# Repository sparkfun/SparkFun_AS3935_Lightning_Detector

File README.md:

SparkFun AS3935 Lightning Detector
========================================

[*SparkFun AS3935 Lightning Detector (SEN-15441)*](https://www.sparkfun.com/products/15441)

The SparkFun Lightning Detector adds lightning detection to your next weather station to make sure you are aware of any potential hazardous weather heading your way. The AS3935 is capable of detecting lightning up to 40km away with an accuracy of 1km to the storm front with a sensitive antenna tuned to pick up lightning events in the 500kHz band. 

There are a number of sources that can cause false positives but the lightning detector itself can reliably filter these out by default. If not, we've made sure to include settings you can configure using the lightning detector library to increase the chip's robustness to noise and false positives. The lightning detector library also gives you access to settings such as storm sensing sensitivity when detecting indoors vs outdoors, or the number of lightning strikes needed to trigger an interrupt.

Repository Contents
-------------------

* **/Documentation** - Datasheets, additional product information
* **/Hardware** - Eagle design files (.brd, .sch)

Documentation
--------------
* **[Installing an Arduino Library](https://learn.sparkfun.com/tutorials/installing-an-arduino-library/)** - Basic instructions on installing an Arduino library
* **[Library](https://github.com/sparkfun/SparkFun_AS3935_Lightning_Detector_Arduino_Library)** - Arduino library for the AS3935 Lightning Detector
* **[Hookup Guide](https://learn.sparkfun.com/tutorials/sparkfun-as3935-lightning-detector-hookup-guide-v20)** - Hookup Guide for the SparkFun AS3935 Lightning Detector

Product Versions
--------------
* [SEN-15441](https://www.sparkfun.com/products/15441) - SparkFun SPI version
* [SEN-15276](https://www.sparkfun.com/products/15276) - SparkFun I2C version
* [SPX-15057](https://www.sparkfun.com/products/retired/15057) - SparkX version

License Information
-------------------

This product is _**open source**_! 

Please review the LICENSE.md file for license information.

If you have any questions or concerns on licensing, please contact technical support on our [SparkFun forums](https://forum.sparkfun.com/viewforum.php?f=152).

Please use, reuse, and modify these files as you see fit. Please maintain attribution to SparkFun Electronics and release under the same license.

Distributed as-is; no warranty is given.

- Your friends at SparkFun.

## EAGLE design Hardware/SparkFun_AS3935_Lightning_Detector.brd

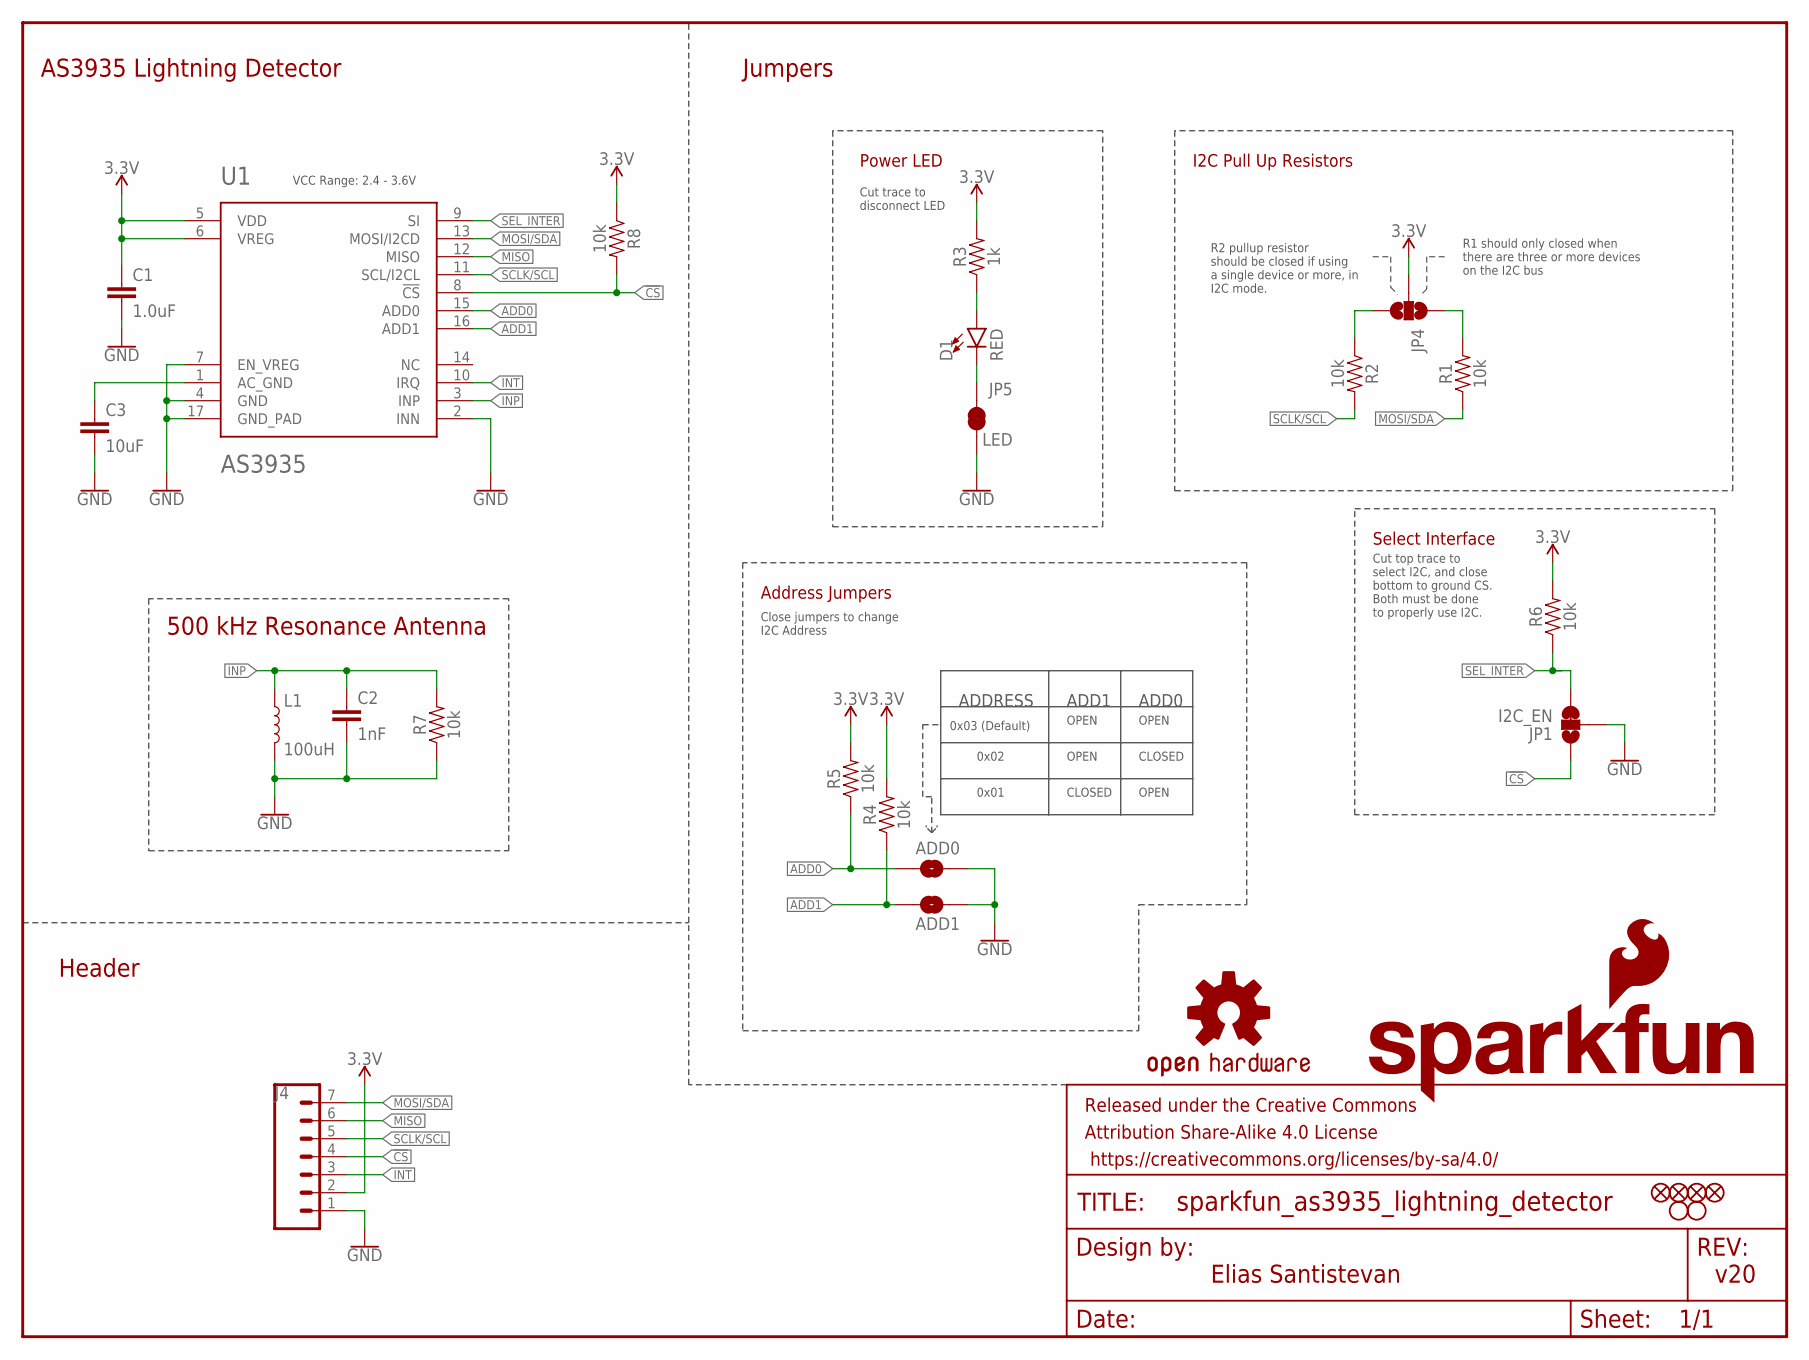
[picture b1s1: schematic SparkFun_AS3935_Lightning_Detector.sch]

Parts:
ADD0, ADD1: JUMPER-SMT_2_NO_SILK; SMT-JUMPER_2_NO_SILK
C1: 1.0uF; 0603
C2: 1nF; 0603
C3: 10uF; 0603
D1: RED; LED-0603
FD1, FD2, FD3, FD4: FIDUCIAL1X2; FIDUCIAL-1X2
FRAME1: FRAME-LETTER; CREATIVE_COMMONS
H1, H2: STAND-OFFTIGHT; STAND-OFF-TIGHT
J4: CONN_07NO_SILK; 1X07_NO_SILK
JP1: I2C_EN; SMT-JUMPER_3_1-NC_TRACE_SILK
JP4: JUMPER-SMT_3_NO_SILK; SMT-JUMPER_3_NO_SILK
JP5: LED; SMT-JUMPER_2_NC_TRACE_SILK
L1: 100uH; MA5532-AE
LOGO1: OSHW-LOGOS; OSHW-LOGO-S
LOGO2: SFE_LOGO_NAME.1_INCH; SFE_LOGO_NAME_.1
LOGO3: SFE_LOGO_FLAME.2_INCH; SFE_LOGO_FLAME_.2
R1, R2, R4, R5, R6, R7, R8: 10k; 0603
R3: 1k; 0603
U1: AS3935; 16LD_MLPQ

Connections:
3.3V: C1.1, J4.2, JP4.2, R3.2, R4.2, R5.2, R6.2, R8.1, U1.5 (VDD), U1.6 (VREG)
!CS: J4.4, JP1.1, R8.2, U1.8 (!CS)
ADD0: ADD0.1, R5.1, U1.15 (ADD0)
ADD1: ADD1.1, R4.1, U1.16 (ADD1)
GND: ADD0.2, ADD1.2, C1.2, C2.2, C3.2, J4.1, JP1.2, JP5.1, L1.2, R7.1, U1.2 (INN), U1.4 (GND), U1.7 (EN_VREG), U1.17 (GND_PAD)
INP: C2.1, L1.1, R7.2, U1.3 (INP)
INT: J4.3, U1.10 (IRQ)
MISO: J4.6, U1.12 (MISO)
MOSI/SDA: J4.7, R1.1, U1.13 (MOSI/I2CD)
unnamed: D1.A, R3.1
unnamed: C3.1, U1.1 (AC_GND)
unnamed: JP4.1, R1.2
unnamed: JP4.3, R2.1
unnamed: D1.C, JP5.2
SCLK/SCL: J4.5, R2.2, U1.11 (SCL/I2CL)
SEL_INTER: JP1.3, R6.1, U1.9 (SI)

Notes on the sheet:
Elias Santistevan
v20
AS3935 Lightning Detector
Jumpers
Header
500 kHz Resonance Antenna
R1 should only closed when there are three or more devices on the I2C bus
Close jumpers to change I2C Address
ADD0
ADD1
OPEN
CLOSED
ADDRESS
0x03 (Default)
0x02
VCC Range: 2.4 - 3.6V
Cut trace to disconnect LED
0x01
R2 pullup resistor should be closed if using a single device or more, in I2C mode.
Power LED
I2C Pull Up Resistors
Address Jumpers
Select Interface
Cut top trace to select I2C, and close bottom to ground CS. Both must be done to properly use I2C.

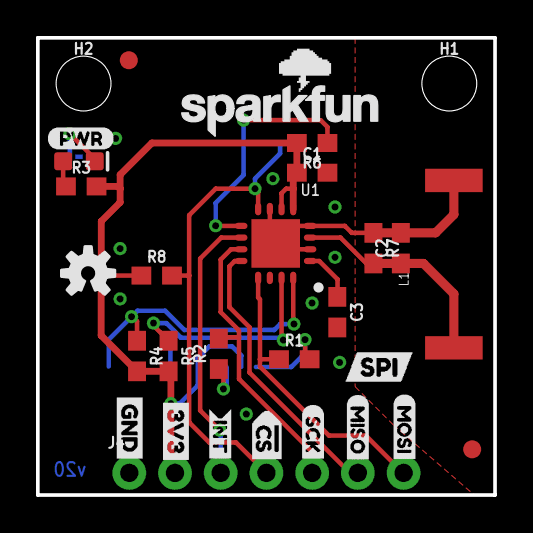
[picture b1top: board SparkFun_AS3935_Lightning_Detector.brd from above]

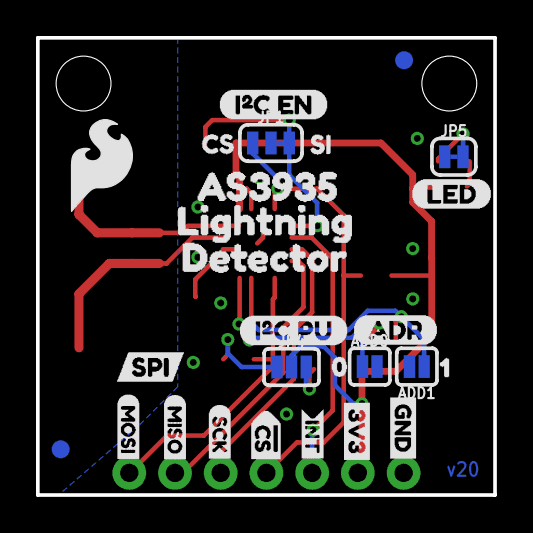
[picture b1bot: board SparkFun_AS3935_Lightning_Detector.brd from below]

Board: 2 copper layers, 25.4 x 25.4 mm, 59 parts (27 on the bottom side), 16 nets.

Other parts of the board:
U$1: LED0
U$2, U$10: GND-03
U$3, U$15: SPI1
U$4, U$18: 3V3-03
U$5, U$30: #CS0
U$6: AS39350
U$7: LIGHTNING0
U$8, U$23: SCK-(]-03
U$9, U$12: MISO-(]-03
U$11, U$22: MOSI-(]-03
U$13, U$14: INT0
U$16: CS0
U$17: I#C_EN0
U$19: SI1
U$32: PWR-()-03
U$33: ADR-()-04
U$34: I#C_PU0
U$36: 10
U$37: 00
U$39: DETECTOR0
U$40: ##0

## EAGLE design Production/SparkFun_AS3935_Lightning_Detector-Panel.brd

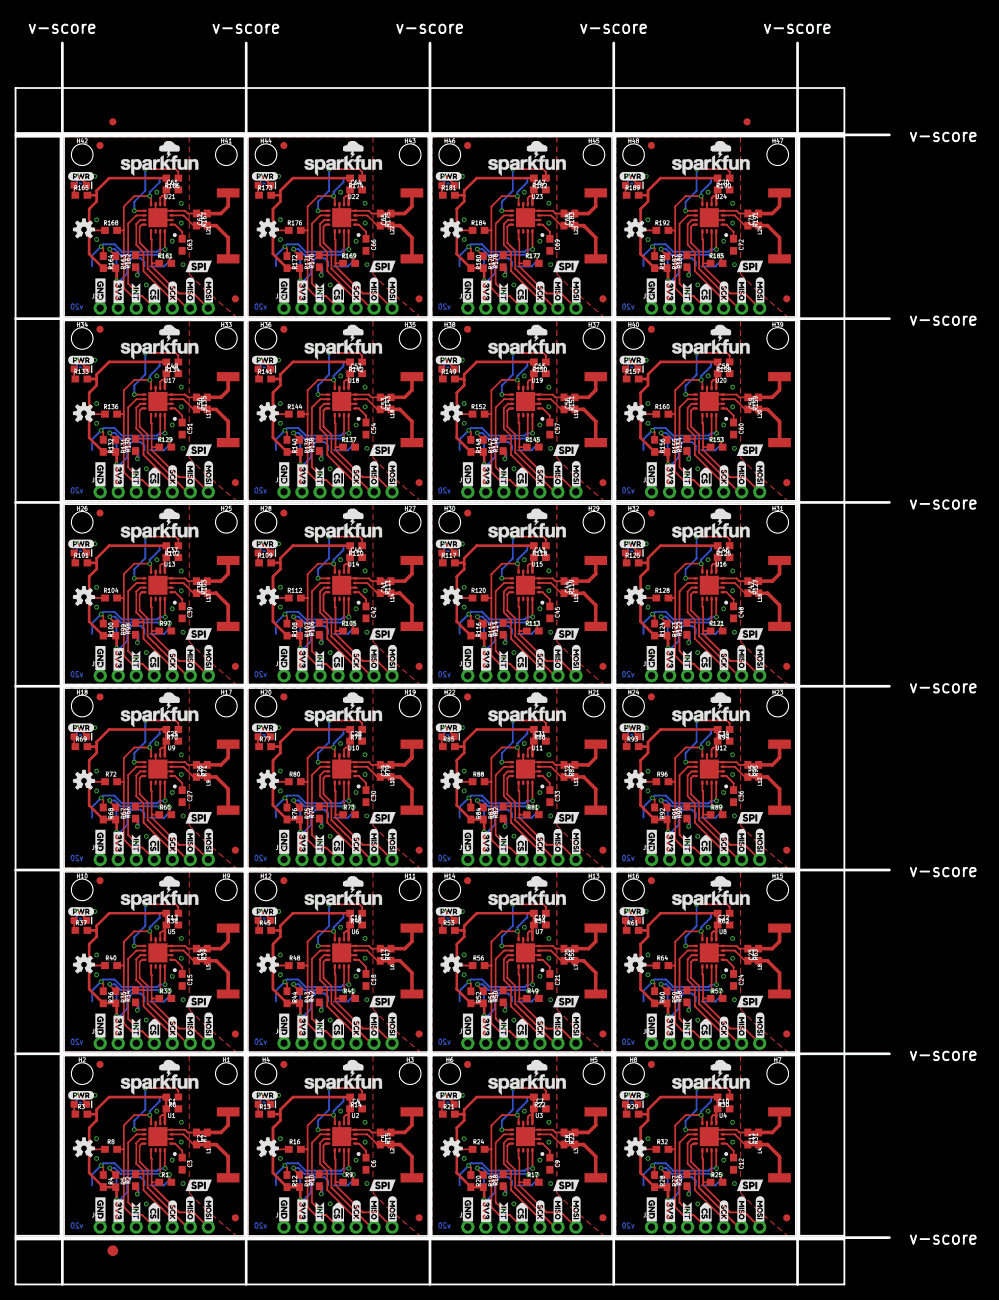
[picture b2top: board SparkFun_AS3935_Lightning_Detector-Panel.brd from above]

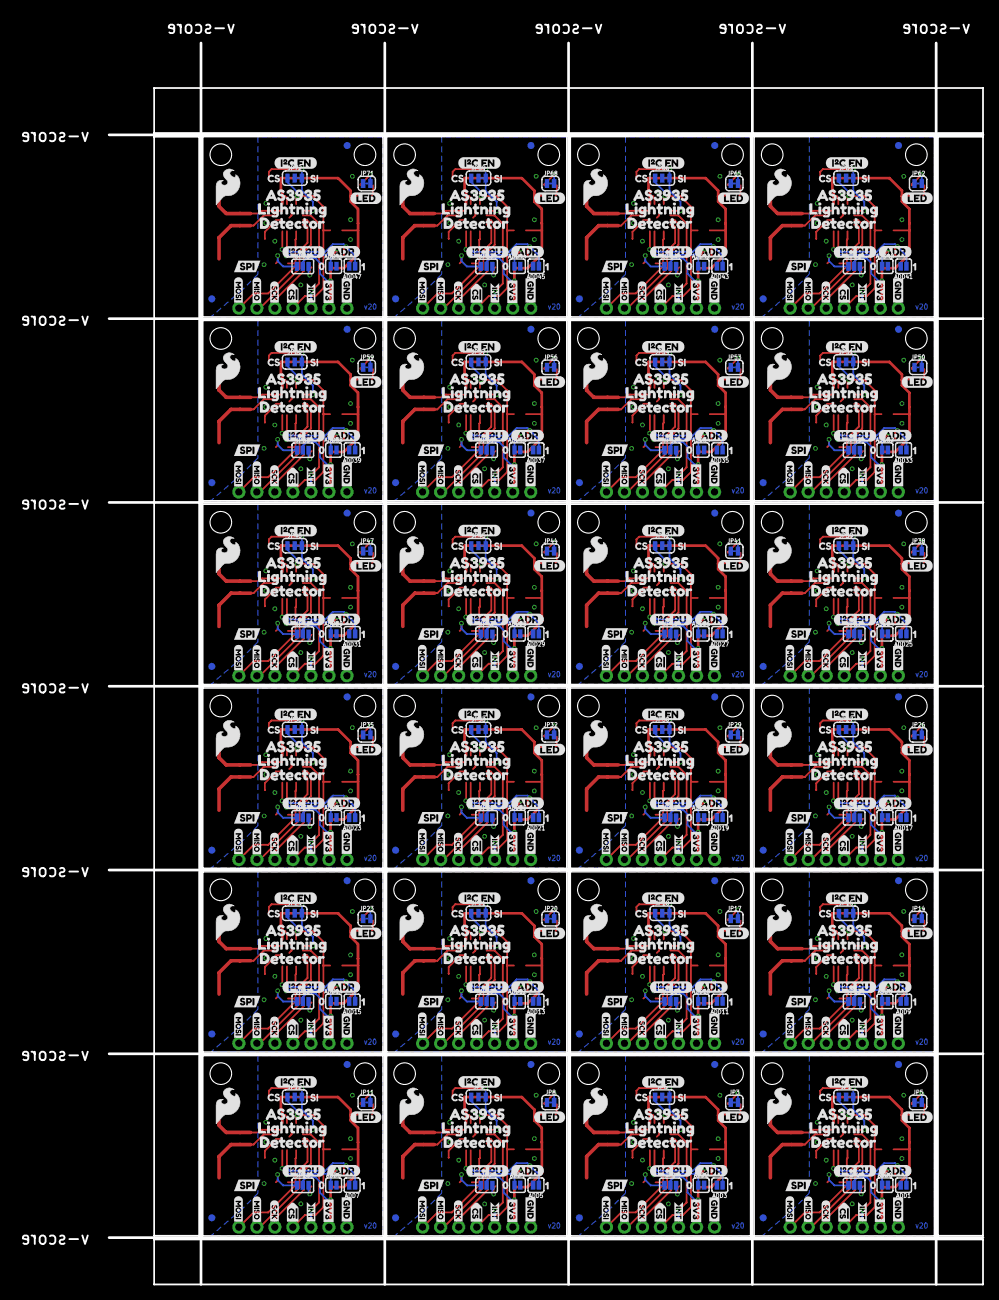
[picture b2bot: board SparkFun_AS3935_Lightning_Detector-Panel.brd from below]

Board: 2 copper layers, 136.4 x 178.9 mm, 1395 parts (648 on the bottom side), 384 nets.

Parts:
ADD0, ADD1, ADD2, ADD3, ADD4, ADD5, ADD6, ADD7, ADD8, ADD9, ADD10, ADD11, ADD12, ADD13, ADD14, ADD15, ADD16, ADD17, ADD18, ADD19, ADD20, ADD21, ADD22, ADD23, ADD24, ADD25, ADD26, ADD27, ADD28, ADD29, ADD30, ADD31, ADD32, ADD33, ADD34, ADD35, ADD36, ADD37, ADD38, ADD39, ADD40, ADD41, ADD42, ADD43, ADD44, ADD45, ADD46, ADD47: JUMPER-SMT_2_NO_SILK; SMT-JUMPER_2_NO_SILK
C1, C4, C7, C10, C13, C16, C19, C22, C25, C28, C31, C34, C37, C40, C43, C46, C49, C52, C55, C58, C61, C64, C67, C70: 1.0uF; 0603
C2, C5, C8, C11, C14, C17, C20, C23, C26, C29, C32, C35, C38, C41, C44, C47, C50, C53, C56, C59, C62, C65, C68, C71: 1nF; 0603
C3, C6, C9, C12, C15, C18, C21, C24, C27, C30, C33, C36, C39, C42, C45, C48, C51, C54, C57, C60, C63, C66, C69, C72: 10uF; 0603
D1, D2, D3, D4, D5, D6, D7, D8, D9, D10, D11, D12, D13, D14, D15, D16, D17, D18, D19, D20, D21, D22, D23, D24: RED; LED-0603
E$1, E$2: FIDUCIAL-1X2
E$3: FIDUCIAL-1.5X3
FD1, FD2, FD3, FD4, FD5, FD6, FD7, FD8, FD9, FD10, FD11, FD12, FD13, FD14, FD15, FD16, FD17, FD18, FD19, FD20, FD21, FD22, FD23, FD24, FD25, FD26, FD27, FD28, FD29, FD30, FD31, FD32, FD33, FD34, FD35, FD36, FD37, FD38, FD39, FD40, FD41, FD42, FD43, FD44, FD45, FD46, FD47, FD48, FD49, FD50, FD51, FD52, FD53, FD54, FD55, FD56, FD57, FD58, FD59, FD60, FD61, FD62, FD63, FD64, FD65, FD66, FD67, FD68, FD69, FD70, FD71, FD72, FD73, FD74, FD75, FD76, FD77, FD78, FD79, FD80, FD81, FD82, FD83, FD84, FD85, FD86, FD87, FD88, FD89, FD90, FD91, FD92, FD93, FD94, FD95, FD96: FIDUCIAL1X2; FIDUCIAL-1X2
H1, H2, H3, H4, H5, H6, H7, H8, H9, H10, H11, H12, H13, H14, H15, H16, H17, H18, H19, H20, H21, H22, H23, H24, H25, H26, H27, H28, H29, H30, H31, H32, H33, H34, H35, H36, H37, H38, H39, H40, H41, H42, H43, H44, H45, H46, H47, H48: STAND-OFFTIGHT; STAND-OFF-TIGHT
J1, J2, J3, J4, J5, J6, J7, J8, J9, J10, J11, J12, J13, J14, J15, J16, J17, J18, J19, J20, J21, J22, J23, J24: 1X07_NO_SILK
JP1, JP6, JP9, JP12, JP15, JP18, JP21, JP24, JP27, JP30, JP33, JP36, JP39, JP42, JP45, JP48, JP51, JP54, JP57, JP60, JP63, JP66, JP69, JP72: I2C_EN; SMT-JUMPER_3_1-NC_TRACE_SILK
JP2, JP4, JP7, JP10, JP13, JP16, JP19, JP22, JP25, JP28, JP31, JP34, JP37, JP40, JP43, JP46, JP49, JP52, JP55, JP58, JP61, JP64, JP67, JP70: JUMPER-SMT_3_NO_SILK; SMT-JUMPER_3_NO_SILK
JP3, JP5, JP8, JP11, JP14, JP17, JP20, JP23, JP26, JP29, JP32, JP35, JP38, JP41, JP44, JP47, JP50, JP53, JP56, JP59, JP62, JP65, JP68, JP71: LED; SMT-JUMPER_2_NC_TRACE_SILK
L1, L2, L3, L4, L5, L6, L7, L8, L9, L10, L11, L12, L13, L14, L15, L16, L17, L18, L19, L20, L21, L22, L23, L24: 100uH; MA5532-AE
LOGO1, LOGO4, LOGO7, LOGO10, LOGO13, LOGO16, LOGO19, LOGO22, LOGO25, LOGO28, LOGO31, LOGO34, LOGO37, LOGO40, LOGO43, LOGO46, LOGO49, LOGO52, LOGO55, LOGO58, LOGO61, LOGO64, LOGO67, LOGO70: OSHW-LOGOS; OSHW-LOGO-S
LOGO2, LOGO5, LOGO8, LOGO11, LOGO14, LOGO17, LOGO20, LOGO23, LOGO26, LOGO29, LOGO32, LOGO35, LOGO38, LOGO41, LOGO44, LOGO47, LOGO50, LOGO53, LOGO56, LOGO59, LOGO62, LOGO65, LOGO68, LOGO71: SFE_LOGO_NAME.1_INCH; SFE_LOGO_NAME_.1
LOGO3, LOGO6, LOGO9, LOGO12, LOGO15, LOGO18, LOGO21, LOGO24, LOGO27, LOGO30, LOGO33, LOGO36, LOGO39, LOGO42, LOGO45, LOGO48, LOGO51, LOGO54, LOGO57, LOGO60, LOGO63, LOGO66, LOGO69, LOGO72: SFE_LOGO_FLAME.2_INCH; SFE_LOGO_FLAME_.2
R1, R2, R4, R5, R6, R7, R8, R9, R10, R11, R12, R14, R15, R16, R17, R18, R19, R20, R22, R23, R24, R25, R26, R27, R28, R30, R31, R32, R33, R34, R35, R36, R38, R39, R40, R41, R42, R43, R44, R46, R47, R48, R49, R50, R51, R52, R54, R55, R56, R57, R58, R59, R60, R62, R63, R64, R65, R66, R67, R68, R70, R71, R72, R73, R74, R75, R76, R78, R79, R80, R81, R82, R83, R84, R86, R87, R88, R89, R90, R91, R92, R94, R95, R96, R97, R98, R99, R100, R102, R103, R104, R105, R106, R107, R108, R110, R111, R112, R113, R114, R115, R116, R118, R119, R120, R121, R122, R123, R124, R126, R127, R128, R129, R130, R131, R132, R134, R135, R136, R137, R138, R139, R140, R142, R143, R144, R145, R146, R147, R148, R150, R151, R152, R153, R154, R155, R156, R158, R159, R160, R161, R162, R163, R164, R166, R167, R168, R169, R170, R171, R172, R174, R175, R176, R177, R178, R179, R180, R182, R183, R184, R185, R186, R187, R188, R190, R191, R192: 10k; 0603
R3, R13, R21, R29, R37, R45, R53, R61, R69, R77, R85, R93, R101, R109, R117, R125, R133, R141, R149, R157, R165, R173, R181, R189: 1k; 0603
U1, U2, U3, U4, U5, U6, U7, U8, U9, U10, U11, U12, U13, U14, U15, U16, U17, U18, U19, U20, U21, U22, U23, U24: AS3935; 16LD_MLPQ
U$1, U$45, U$74, U$103, U$132, U$161, U$190, U$219, U$248, U$277, U$306, U$335, U$364, U$393, U$422, U$451, U$480, U$509, U$538, U$567, U$596, U$625, U$654, U$683: LED0
U$2, U$10, U$20, U$47, U$59, U$76, U$88, U$105, U$117, U$134, U$146, U$163, U$175, U$192, U$204, U$221, U$233, U$250, U$262, U$279, U$291, U$308, U$320, U$337, U$349, U$366, U$378, U$395, U$407, U$424, U$436, U$453, U$465, U$482, U$494, U$511, U$523, U$540, U$552, U$569, U$581, U$598, U$610, U$627, U$639, U$656, U$668, U$685: GND-03
U$3, U$15, U$46, U$53, U$75, U$82, U$104, U$111, U$133, U$140, U$162, U$169, U$191, U$198, U$220, U$227, U$249, U$256, U$278, U$285, U$307, U$314, U$336, U$343, U$365, U$372, U$394, U$401, U$423, U$430, U$452, U$459, U$481, U$488, U$510, U$517, U$539, U$546, U$568, U$575, U$597, U$604, U$626, U$633, U$655, U$662, U$684, U$691: SPI1
U$4, U$18, U$24, U$48, U$61, U$77, U$90, U$106, U$119, U$135, U$148, U$164, U$177, U$193, U$206, U$222, U$235, U$251, U$264, U$280, U$293, U$309, U$322, U$338, U$351, U$367, U$380, U$396, U$409, U$425, U$438, U$454, U$467, U$483, U$496, U$512, U$525, U$541, U$554, U$570, U$583, U$599, U$612, U$628, U$641, U$657, U$670, U$686: 3V3-03
U$5, U$30, U$44, U$49, U$73, U$78, U$102, U$107, U$131, U$136, U$160, U$165, U$189, U$194, U$218, U$223, U$247, U$252, U$276, U$281, U$305, U$310, U$334, U$339, U$363, U$368, U$392, U$397, U$421, U$426, U$450, U$455, U$479, U$484, U$508, U$513, U$537, U$542, U$566, U$571, U$595, U$600, U$624, U$629, U$653, U$658, U$682, U$687: #CS0
U$6, U$31, U$67, U$96, U$125, U$154, U$183, U$212, U$241, U$270, U$299, U$328, U$357, U$386, U$415, U$444, U$473, U$502, U$531, U$560, U$589, U$618, U$647, U$676: AS39350
U$7, U$35, U$68, U$97, U$126, U$155, U$184, U$213, U$242, U$271, U$300, U$329, U$358, U$387, U$416, U$445, U$474, U$503, U$532, U$561, U$590, U$619, U$648, U$677: LIGHTNING0
U$8, U$23, U$43, U$50, U$72, U$79, U$101, U$108, U$130, U$137, U$159, U$166, U$188, U$195, U$217, U$224, U$246, U$253, U$275, U$282, U$304, U$311, U$333, U$340, U$362, U$369, U$391, U$398, U$420, U$427, U$449, U$456, U$478, U$485, U$507, U$514, U$536, U$543, U$565, U$572, U$594, U$601, U$623, U$630, U$652, U$659, U$681, U$688: SCK-(]-03
U$9, U$12, U$21, U$51, U$60, U$80, U$89, U$109, U$118, U$138, U$147, U$167, U$176, U$196, U$205, U$225, U$234, U$254, U$263, U$283, U$292, U$312, U$321, U$341, U$350, U$370, U$379, U$399, U$408, U$428, U$437, U$457, U$466, U$486, U$495, U$515, U$524, U$544, U$553, U$573, U$582, U$602, U$611, U$631, U$640, U$660, U$669, U$689: MISO-(]-03
U$11, U$22, U$42, U$52, U$71, U$81, U$100, U$110, U$129, U$139, U$158, U$168, U$187, U$197, U$216, U$226, U$245, U$255, U$274, U$284, U$303, U$313, U$332, U$342, U$361, U$371, U$390, U$400, U$419, U$429, U$448, U$458, U$477, U$487, U$506, U$516, U$535, U$545, U$564, U$574, U$593, U$603, U$622, U$632, U$651, U$661, U$680, U$690: MOSI-(]-03
U$13, U$14, U$57, U$58, U$86, U$87, U$115, U$116, U$144, U$145, U$173, U$174, U$202, U$203, U$231, U$232, U$260, U$261, U$289, U$290, U$318, U$319, U$347, U$348, U$376, U$377, U$405, U$406, U$434, U$435, U$463, U$464, U$492, U$493, U$521, U$522, U$550, U$551, U$579, U$580, U$608, U$609, U$637, U$638, U$666, U$667, U$695, U$696: INT0
U$16, U$55, U$84, U$113, U$142, U$171, U$200, U$229, U$258, U$287, U$316, U$345, U$374, U$403, U$432, U$461, U$490, U$519, U$548, U$577, U$606, U$635, U$664, U$693: CS0
U$17, U$54, U$83, U$112, U$141, U$170, U$199, U$228, U$257, U$286, U$315, U$344, U$373, U$402, U$431, U$460, U$489, U$518, U$547, U$576, U$605, U$634, U$663, U$692: I#C_EN0
U$19, U$56, U$85, U$114, U$143, U$172, U$201, U$230, U$259, U$288, U$317, U$346, U$375, U$404, U$433, U$462, U$491, U$520, U$549, U$578, U$607, U$636, U$665, U$694: SI1
U$25, U$32, U$62, U$91, U$120, U$149, U$178, U$207, U$236, U$265, U$294, U$323, U$352, U$381, U$410, U$439, U$468, U$497, U$526, U$555, U$584, U$613, U$642, U$671: PWR-()-03
U$26, U$33, U$63, U$92, U$121, U$150, U$179, U$208, U$237, U$266, U$295, U$324, U$353, U$382, U$411, U$440, U$469, U$498, U$527, U$556, U$585, U$614, U$643, U$672: ADR-()-04
U$27, U$34, U$64, U$93, U$122, U$151, U$180, U$209, U$238, U$267, U$296, U$325, U$354, U$383, U$412, U$441, U$470, U$499, U$528, U$557, U$586, U$615, U$644, U$673: I#C_PU0
U$28, U$36, U$65, U$94, U$123, U$152, U$181, U$210, U$239, U$268, U$297, U$326, U$355, U$384, U$413, U$442, U$471, U$500, U$529, U$558, U$587, U$616, U$645, U$674: 10
U$29, U$37, U$66, U$95, U$124, U$153, U$182, U$211, U$240, U$269, U$298, U$327, U$356, U$385, U$414, U$443, U$472, U$501, U$530, U$559, U$588, U$617, U$646, U$675: 00
U$38, U$39, U$69, U$98, U$127, U$156, U$185, U$214, U$243, U$272, U$301, U$330, U$359, U$388, U$417, U$446, U$475, U$504, U$533, U$562, U$591, U$620, U$649, U$678: DETECTOR0
U$40, U$41, U$70, U$99, U$128, U$157, U$186, U$215, U$244, U$273, U$302, U$331, U$360, U$389, U$418, U$447, U$476, U$505, U$534, U$563, U$592, U$621, U$650, U$679: ##0

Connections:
3.3V: C1.1, J4.2, JP4.2, R3.2, R4.2, R5.2, R6.2, R8.1, U1.5, U1.6
3.3V1: C4.1, J1.2, JP2.2, R11.2, R12.2, R13.2, R14.2, R16.1, U2.5, U2.6
3.3V2: C7.1, J2.2, JP7.2, R19.2, R20.2, R21.2, R22.2, R24.1, U3.5, U3.6
3.3V3: C10.1, J3.2, JP10.2, R27.2, R28.2, R29.2, R30.2, R32.1, U4.5, U4.6
3.3V4: C13.1, J5.2, JP13.2, R35.2, R36.2, R37.2, R38.2, R40.1, U5.5, U5.6
3.3V5: C16.1, J6.2, JP16.2, R43.2, R44.2, R45.2, R46.2, R48.1, U6.5, U6.6
3.3V6: C19.1, J7.2, JP19.2, R51.2, R52.2, R53.2, R54.2, R56.1, U7.5, U7.6
3.3V7: C22.1, J8.2, JP22.2, R59.2, R60.2, R61.2, R62.2, R64.1, U8.5, U8.6
3.3V8: C25.1, J9.2, JP25.2, R67.2, R68.2, R69.2, R70.2, R72.1, U9.5, U9.6
3.3V9: C28.1, J10.2, JP28.2, R75.2, R76.2, R77.2, R78.2, R80.1, U10.5, U10.6
3.3V10: C31.1, J11.2, JP31.2, R83.2, R84.2, R85.2, R86.2, R88.1, U11.5, U11.6
3.3V11: C34.1, J12.2, JP34.2, R91.2, R92.2, R93.2, R94.2, R96.1, U12.5, U12.6
3.3V12: C37.1, J13.2, JP37.2, R99.2, R100.2, R101.2, R102.2, R104.1, U13.5, U13.6
3.3V13: C40.1, J14.2, JP40.2, R107.2, R108.2, R109.2, R110.2, R112.1, U14.5, U14.6
3.3V14: C43.1, J15.2, JP43.2, R115.2, R116.2, R117.2, R118.2, R120.1, U15.5, U15.6
3.3V15: C46.1, J16.2, JP46.2, R123.2, R124.2, R125.2, R126.2, R128.1, U16.5, U16.6
3.3V16: C49.1, J17.2, JP49.2, R131.2, R132.2, R133.2, R134.2, R136.1, U17.5, U17.6
3.3V17: C52.1, J18.2, JP52.2, R139.2, R140.2, R141.2, R142.2, R144.1, U18.5, U18.6
3.3V18: C55.1, J19.2, JP55.2, R147.2, R148.2, R149.2, R150.2, R152.1, U19.5, U19.6
3.3V19: C58.1, J20.2, JP58.2, R155.2, R156.2, R157.2, R158.2, R160.1, U20.5, U20.6
3.3V20: C61.1, J21.2, JP61.2, R163.2, R164.2, R165.2, R166.2, R168.1, U21.5, U21.6
3.3V21: C64.1, J22.2, JP64.2, R171.2, R172.2, R173.2, R174.2, R176.1, U22.5, U22.6
3.3V22: C67.1, J23.2, JP67.2, R179.2, R180.2, R181.2, R182.2, R184.1, U23.5, U23.6
3.3V23: C70.1, J24.2, JP70.2, R187.2, R188.2, R189.2, R190.2, R192.1, U24.5, U24.6
!CS: J4.4, JP1.1, R8.2, U1.8
!CS1: J1.4, JP6.1, R16.2, U2.8
!CS2: J2.4, JP9.1, R24.2, U3.8
!CS3: J3.4, JP12.1, R32.2, U4.8
!CS4: J5.4, JP15.1, R40.2, U5.8
!CS5: J6.4, JP18.1, R48.2, U6.8
!CS6: J7.4, JP21.1, R56.2, U7.8
!CS7: J8.4, JP24.1, R64.2, U8.8
!CS8: J9.4, JP27.1, R72.2, U9.8
!CS9: J10.4, JP30.1, R80.2, U10.8
!CS10: J11.4, JP33.1, R88.2, U11.8
!CS11: J12.4, JP36.1, R96.2, U12.8
!CS12: J13.4, JP39.1, R104.2, U13.8
!CS13: J14.4, JP42.1, R112.2, U14.8
!CS14: J15.4, JP45.1, R120.2, U15.8
!CS15: J16.4, JP48.1, R128.2, U16.8
!CS16: J17.4, JP51.1, R136.2, U17.8
!CS17: J18.4, JP54.1, R144.2, U18.8
!CS18: J19.4, JP57.1, R152.2, U19.8
!CS19: J20.4, JP60.1, R160.2, U20.8
!CS20: J21.4, JP63.1, R168.2, U21.8
!CS21: J22.4, JP66.1, R176.2, U22.8
!CS22: J23.4, JP69.1, R184.2, U23.8
!CS23: J24.4, JP72.1, R192.2, U24.8
ADD0: ADD0.1, R5.1, U1.15
ADD1: ADD1.1, R4.1, U1.16
ADD2: ADD2.1, R11.1, U2.15
ADD3: ADD3.1, R12.1, U2.16
ADD4: ADD4.1, R19.1, U3.15
ADD5: ADD5.1, R20.1, U3.16
ADD6: ADD6.1, R27.1, U4.15
ADD7: ADD7.1, R28.1, U4.16
ADD8: ADD8.1, R35.1, U5.15
ADD9: ADD9.1, R36.1, U5.16
ADD10: ADD10.1, R43.1, U6.15
ADD11: ADD11.1, R44.1, U6.16
ADD12: ADD12.1, R51.1, U7.15
ADD13: ADD13.1, R52.1, U7.16
ADD14: ADD14.1, R59.1, U8.15
ADD15: ADD15.1, R60.1, U8.16
ADD16: ADD16.1, R67.1, U9.15
ADD17: ADD17.1, R68.1, U9.16
ADD18: ADD18.1, R75.1, U10.15
ADD19: ADD19.1, R76.1, U10.16
ADD20: ADD20.1, R83.1, U11.15
ADD21: ADD21.1, R84.1, U11.16
ADD22: ADD22.1, R91.1, U12.15
ADD23: ADD23.1, R92.1, U12.16
ADD24: ADD24.1, R99.1, U13.15
ADD25: ADD25.1, R100.1, U13.16
ADD26: ADD26.1, R107.1, U14.15
ADD27: ADD27.1, R108.1, U14.16
ADD28: ADD28.1, R115.1, U15.15
ADD29: ADD29.1, R116.1, U15.16
ADD30: ADD30.1, R123.1, U16.15
ADD31: ADD31.1, R124.1, U16.16
ADD32: ADD32.1, R131.1, U17.15
ADD33: ADD33.1, R132.1, U17.16
ADD34: ADD34.1, R139.1, U18.15
ADD35: ADD35.1, R140.1, U18.16
ADD36: ADD36.1, R147.1, U19.15
ADD37: ADD37.1, R148.1, U19.16
ADD38: ADD38.1, R155.1, U20.15
ADD39: ADD39.1, R156.1, U20.16
ADD40: ADD40.1, R163.1, U21.15
ADD41: ADD41.1, R164.1, U21.16
ADD42: ADD42.1, R171.1, U22.15
ADD43: ADD43.1, R172.1, U22.16
ADD44: ADD44.1, R179.1, U23.15
ADD45: ADD45.1, R180.1, U23.16
ADD46: ADD46.1, R187.1, U24.15
ADD47: ADD47.1, R188.1, U24.16
GND: ADD0.2, ADD1.2, C1.2, C2.2, C3.2, J4.1, JP1.2, JP5.1, L1.2, R7.1, U1.2, U1.4, U1.7, U1.17
GND1: ADD2.2, ADD3.2, C4.2, C5.2, C6.2, J1.1, JP3.1, JP6.2, L2.2, R15.1, U2.2, U2.4, U2.7, U2.17
GND2: ADD4.2, ADD5.2, C7.2, C8.2, C9.2, J2.1, JP8.1, JP9.2, L3.2, R23.1, U3.2, U3.4, U3.7, U3.17
GND3: ADD6.2, ADD7.2, C10.2, C11.2, C12.2, J3.1, JP11.1, JP12.2, L4.2, R31.1, U4.2, U4.4, U4.7, U4.17
GND4: ADD8.2, ADD9.2, C13.2, C14.2, C15.2, J5.1, JP14.1, JP15.2, L5.2, R39.1, U5.2, U5.4, U5.7, U5.17
GND5: ADD10.2, ADD11.2, C16.2, C17.2, C18.2, J6.1, JP17.1, JP18.2, L6.2, R47.1, U6.2, U6.4, U6.7, U6.17
GND6: ADD12.2, ADD13.2, C19.2, C20.2, C21.2, J7.1, JP20.1, JP21.2, L7.2, R55.1, U7.2, U7.4, U7.7, U7.17
GND7: ADD14.2, ADD15.2, C22.2, C23.2, C24.2, J8.1, JP23.1, JP24.2, L8.2, R63.1, U8.2, U8.4, U8.7, U8.17
GND8: ADD16.2, ADD17.2, C25.2, C26.2, C27.2, J9.1, JP26.1, JP27.2, L9.2, R71.1, U9.2, U9.4, U9.7, U9.17
GND9: ADD18.2, ADD19.2, C28.2, C29.2, C30.2, J10.1, JP29.1, JP30.2, L10.2, R79.1, U10.2, U10.4, U10.7, U10.17
GND10: ADD20.2, ADD21.2, C31.2, C32.2, C33.2, J11.1, JP32.1, JP33.2, L11.2, R87.1, U11.2, U11.4, U11.7, U11.17
GND11: ADD22.2, ADD23.2, C34.2, C35.2, C36.2, J12.1, JP35.1, JP36.2, L12.2, R95.1, U12.2, U12.4, U12.7, U12.17
GND12: ADD24.2, ADD25.2, C37.2, C38.2, C39.2, J13.1, JP38.1, JP39.2, L13.2, R103.1, U13.2, U13.4, U13.7, U13.17
GND13: ADD26.2, ADD27.2, C40.2, C41.2, C42.2, J14.1, JP41.1, JP42.2, L14.2, R111.1, U14.2, U14.4, U14.7, U14.17
GND14: ADD28.2, ADD29.2, C43.2, C44.2, C45.2, J15.1, JP44.1, JP45.2, L15.2, R119.1, U15.2, U15.4, U15.7, U15.17
GND15: ADD30.2, ADD31.2, C46.2, C47.2, C48.2, J16.1, JP47.1, JP48.2, L16.2, R127.1, U16.2, U16.4, U16.7, U16.17
GND16: ADD32.2, ADD33.2, C49.2, C50.2, C51.2, J17.1, JP50.1, JP51.2, L17.2, R135.1, U17.2, U17.4, U17.7, U17.17
GND17: ADD34.2, ADD35.2, C52.2, C53.2, C54.2, J18.1, JP53.1, JP54.2, L18.2, R143.1, U18.2, U18.4, U18.7, U18.17
GND18: ADD36.2, ADD37.2, C55.2, C56.2, C57.2, J19.1, JP56.1, JP57.2, L19.2, R151.1, U19.2, U19.4, U19.7, U19.17
GND19: ADD38.2, ADD39.2, C58.2, C59.2, C60.2, J20.1, JP59.1, JP60.2, L20.2, R159.1, U20.2, U20.4, U20.7, U20.17
GND20: ADD40.2, ADD41.2, C61.2, C62.2, C63.2, J21.1, JP62.1, JP63.2, L21.2, R167.1, U21.2, U21.4, U21.7, U21.17
GND21: ADD42.2, ADD43.2, C64.2, C65.2, C66.2, J22.1, JP65.1, JP66.2, L22.2, R175.1, U22.2, U22.4, U22.7, U22.17
GND22: ADD44.2, ADD45.2, C67.2, C68.2, C69.2, J23.1, JP68.1, JP69.2, L23.2, R183.1, U23.2, U23.4, U23.7, U23.17
GND23: ADD46.2, ADD47.2, C70.2, C71.2, C72.2, J24.1, JP71.1, JP72.2, L24.2, R191.1, U24.2, U24.4, U24.7, U24.17
INP: C2.1, L1.1, R7.2, U1.3
INP1: C5.1, L2.1, R15.2, U2.3
INP2: C8.1, L3.1, R23.2, U3.3
INP3: C11.1, L4.1, R31.2, U4.3
INP4: C14.1, L5.1, R39.2, U5.3
INP5: C17.1, L6.1, R47.2, U6.3
INP6: C20.1, L7.1, R55.2, U7.3
INP7: C23.1, L8.1, R63.2, U8.3
INP8: C26.1, L9.1, R71.2, U9.3
INP9: C29.1, L10.1, R79.2, U10.3
INP10: C32.1, L11.1, R87.2, U11.3
INP11: C35.1, L12.1, R95.2, U12.3
INP12: C38.1, L13.1, R103.2, U13.3
INP13: C41.1, L14.1, R111.2, U14.3
INP14: C44.1, L15.1, R119.2, U15.3
INP15: C47.1, L16.1, R127.2, U16.3
INP16: C50.1, L17.1, R135.2, U17.3
INP17: C53.1, L18.1, R143.2, U18.3
INP18: C56.1, L19.1, R151.2, U19.3
INP19: C59.1, L20.1, R159.2, U20.3
INP20: C62.1, L21.1, R167.2, U21.3
INP21: C65.1, L22.1, R175.2, U22.3
INP22: C68.1, L23.1, R183.2, U23.3
INP23: C71.1, L24.1, R191.2, U24.3
INT: J4.3, U1.10
INT1: J1.3, U2.10
INT2: J2.3, U3.10
INT3: J3.3, U4.10
INT4: J5.3, U5.10
INT5: J6.3, U6.10
INT6: J7.3, U7.10
INT7: J8.3, U8.10
INT8: J9.3, U9.10
INT9: J10.3, U10.10
INT10: J11.3, U11.10
INT11: J12.3, U12.10
INT12: J13.3, U13.10
INT13: J14.3, U14.10
INT14: J15.3, U15.10
INT15: J16.3, U16.10
INT16: J17.3, U17.10
INT17: J18.3, U18.10
INT18: J19.3, U19.10
INT19: J20.3, U20.10
INT20: J21.3, U21.10
INT21: J22.3, U22.10
INT22: J23.3, U23.10
INT23: J24.3, U24.10
MISO: J4.6, U1.12
MISO1: J1.6, U2.12
MISO2: J2.6, U3.12
MISO3: J3.6, U4.12
MISO4: J5.6, U5.12
MISO5: J6.6, U6.12
MISO6: J7.6, U7.12
MISO7: J8.6, U8.12
MISO8: J9.6, U9.12
MISO9: J10.6, U10.12
MISO10: J11.6, U11.12
MISO11: J12.6, U12.12
MISO12: J13.6, U13.12
MISO13: J14.6, U14.12
MISO14: J15.6, U15.12
MISO15: J16.6, U16.12
MISO16: J17.6, U17.12
MISO17: J18.6, U18.12
MISO18: J19.6, U19.12
MISO19: J20.6, U20.12
MISO20: J21.6, U21.12
MISO21: J22.6, U22.12
MISO22: J23.6, U23.12
MISO23: J24.6, U24.12
MOSI/SDA: J4.7, R1.1, U1.13
MOSI/SDA1: J1.7, R9.1, U2.13
MOSI/SDA2: J2.7, R17.1, U3.13
MOSI/SDA3: J3.7, R25.1, U4.13
MOSI/SDA4: J5.7, R33.1, U5.13
MOSI/SDA5: J6.7, R41.1, U6.13
MOSI/SDA6: J7.7, R49.1, U7.13
MOSI/SDA7: J8.7, R57.1, U8.13
MOSI/SDA8: J9.7, R65.1, U9.13
MOSI/SDA9: J10.7, R73.1, U10.13
MOSI/SDA10: J11.7, R81.1, U11.13
MOSI/SDA11: J12.7, R89.1, U12.13
MOSI/SDA12: J13.7, R97.1, U13.13
MOSI/SDA13: J14.7, R105.1, U14.13
MOSI/SDA14: J15.7, R113.1, U15.13
MOSI/SDA15: J16.7, R121.1, U16.13
MOSI/SDA16: J17.7, R129.1, U17.13
MOSI/SDA17: J18.7, R137.1, U18.13
MOSI/SDA18: J19.7, R145.1, U19.13
MOSI/SDA19: J20.7, R153.1, U20.13
MOSI/SDA20: J21.7, R161.1, U21.13
MOSI/SDA21: J22.7, R169.1, U22.13
MOSI/SDA22: J23.7, R177.1, U23.13
MOSI/SDA23: J24.7, R185.1, U24.13
unnamed: D1.A, R3.1
unnamed: C3.1, U1.1
unnamed: JP4.1, R1.2
unnamed: JP4.3, R2.1
unnamed: D1.C, JP5.2
unnamed: C6.1, U2.1
unnamed: JP2.1, R9.2
unnamed: JP2.3, R10.1
unnamed: D2.A, R13.1
unnamed: D2.C, JP3.2
unnamed: C9.1, U3.1
unnamed: JP7.1, R17.2
unnamed: JP7.3, R18.1
unnamed: D3.A, R21.1
unnamed: D3.C, JP8.2
unnamed: C12.1, U4.1
unnamed: JP10.1, R25.2
unnamed: JP10.3, R26.1
unnamed: D4.A, R29.1
unnamed: D4.C, JP11.2
unnamed: C15.1, U5.1
unnamed: JP13.1, R33.2
unnamed: JP13.3, R34.1
unnamed: D5.A, R37.1
unnamed: D5.C, JP14.2
unnamed: C18.1, U6.1
unnamed: JP16.1, R41.2
unnamed: JP16.3, R42.1
unnamed: D6.A, R45.1
unnamed: D6.C, JP17.2
unnamed: C21.1, U7.1
unnamed: JP19.1, R49.2
unnamed: JP19.3, R50.1
unnamed: D7.A, R53.1
unnamed: D7.C, JP20.2
unnamed: C24.1, U8.1
unnamed: JP22.1, R57.2
unnamed: JP22.3, R58.1
unnamed: D8.A, R61.1
unnamed: D8.C, JP23.2
unnamed: C27.1, U9.1
unnamed: JP25.1, R65.2
unnamed: JP25.3, R66.1
unnamed: D9.A, R69.1
unnamed: D9.C, JP26.2
unnamed: C30.1, U10.1
unnamed: JP28.1, R73.2
unnamed: JP28.3, R74.1
unnamed: D10.A, R77.1
unnamed: D10.C, JP29.2
unnamed: C33.1, U11.1
unnamed: JP31.1, R81.2
unnamed: JP31.3, R82.1
unnamed: D11.A, R85.1
unnamed: D11.C, JP32.2
unnamed: C36.1, U12.1
unnamed: JP34.1, R89.2
unnamed: JP34.3, R90.1
unnamed: D12.A, R93.1
unnamed: D12.C, JP35.2
unnamed: C39.1, U13.1
unnamed: JP37.1, R97.2
unnamed: JP37.3, R98.1
unnamed: D13.A, R101.1
unnamed: D13.C, JP38.2
unnamed: C42.1, U14.1
unnamed: JP40.1, R105.2
unnamed: JP40.3, R106.1
unnamed: D14.A, R109.1
unnamed: D14.C, JP41.2
unnamed: C45.1, U15.1
unnamed: JP43.1, R113.2
unnamed: JP43.3, R114.1
unnamed: D15.A, R117.1
unnamed: D15.C, JP44.2
unnamed: C48.1, U16.1
unnamed: JP46.1, R121.2
unnamed: JP46.3, R122.1
unnamed: D16.A, R125.1
unnamed: D16.C, JP47.2
unnamed: C51.1, U17.1
unnamed: JP49.1, R129.2
unnamed: JP49.3, R130.1
unnamed: D17.A, R133.1
unnamed: D17.C, JP50.2
unnamed: C54.1, U18.1
unnamed: JP52.1, R137.2
unnamed: JP52.3, R138.1
unnamed: D18.A, R141.1
unnamed: D18.C, JP53.2
unnamed: C57.1, U19.1
unnamed: JP55.1, R145.2
unnamed: JP55.3, R146.1
unnamed: D19.A, R149.1
unnamed: D19.C, JP56.2
unnamed: C60.1, U20.1
unnamed: JP58.1, R153.2
unnamed: JP58.3, R154.1
unnamed: D20.A, R157.1
unnamed: D20.C, JP59.2
unnamed: C63.1, U21.1
unnamed: JP61.1, R161.2
unnamed: JP61.3, R162.1
unnamed: D21.A, R165.1
unnamed: D21.C, JP62.2
unnamed: C66.1, U22.1
unnamed: JP64.1, R169.2
unnamed: JP64.3, R170.1
unnamed: D22.A, R173.1
unnamed: D22.C, JP65.2
unnamed: C69.1, U23.1
unnamed: JP67.1, R177.2
unnamed: JP67.3, R178.1
unnamed: D23.A, R181.1
unnamed: D23.C, JP68.2
unnamed: C72.1, U24.1
unnamed: JP70.1, R185.2
unnamed: JP70.3, R186.1
unnamed: D24.A, R189.1
unnamed: D24.C, JP71.2
SCLK/SCL: J4.5, R2.2, U1.11
SCLK/SCL1: J1.5, R10.2, U2.11
SCLK/SCL2: J2.5, R18.2, U3.11
SCLK/SCL3: J3.5, R26.2, U4.11
SCLK/SCL4: J5.5, R34.2, U5.11
SCLK/SCL5: J6.5, R42.2, U6.11
SCLK/SCL6: J7.5, R50.2, U7.11
SCLK/SCL7: J8.5, R58.2, U8.11
SCLK/SCL8: J9.5, R66.2, U9.11
SCLK/SCL9: J10.5, R74.2, U10.11
SCLK/SCL10: J11.5, R82.2, U11.11
SCLK/SCL11: J12.5, R90.2, U12.11
SCLK/SCL12: J13.5, R98.2, U13.11
SCLK/SCL13: J14.5, R106.2, U14.11
SCLK/SCL14: J15.5, R114.2, U15.11
SCLK/SCL15: J16.5, R122.2, U16.11
SCLK/SCL16: J17.5, R130.2, U17.11
SCLK/SCL17: J18.5, R138.2, U18.11
SCLK/SCL18: J19.5, R146.2, U19.11
SCLK/SCL19: J20.5, R154.2, U20.11
SCLK/SCL20: J21.5, R162.2, U21.11
SCLK/SCL21: J22.5, R170.2, U22.11
SCLK/SCL22: J23.5, R178.2, U23.11
SCLK/SCL23: J24.5, R186.2, U24.11
SEL_INTER: JP1.3, R6.1, U1.9
SEL_INTER1: JP6.3, R14.1, U2.9
SEL_INTER2: JP9.3, R22.1, U3.9
SEL_INTER3: JP12.3, R30.1, U4.9
SEL_INTER4: JP15.3, R38.1, U5.9
SEL_INTER5: JP18.3, R46.1, U6.9
SEL_INTER6: JP21.3, R54.1, U7.9
SEL_INTER7: JP24.3, R62.1, U8.9
SEL_INTER8: JP27.3, R70.1, U9.9
SEL_INTER9: JP30.3, R78.1, U10.9
SEL_INTER10: JP33.3, R86.1, U11.9
SEL_INTER11: JP36.3, R94.1, U12.9
SEL_INTER12: JP39.3, R102.1, U13.9
SEL_INTER13: JP42.3, R110.1, U14.9
SEL_INTER14: JP45.3, R118.1, U15.9
SEL_INTER15: JP48.3, R126.1, U16.9
SEL_INTER16: JP51.3, R134.1, U17.9
SEL_INTER17: JP54.3, R142.1, U18.9
SEL_INTER18: JP57.3, R150.1, U19.9
SEL_INTER19: JP60.3, R158.1, U20.9
SEL_INTER20: JP63.3, R166.1, U21.9
SEL_INTER21: JP66.3, R174.1, U22.9
SEL_INTER22: JP69.3, R182.1, U23.9
SEL_INTER23: JP72.3, R190.1, U24.9

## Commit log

2019-03-01 Initial Commit - transfered files from SparkX repo
2019-03-01 Adds SparkFun related silk, adds parts that were added to Eagle libraries
2019-03-05 Replaces lightning detector - lightning detector was moved to correct library and so needed to be replaced in design
    * Changes pull up resistor on the select interface line with a 10k
    * Changes the wording of the address info box in the schematic to open/close rather
    than high/low
2019-03-05 Fixes clearance issues after changing DRC to SparkFun-tight.drc, Adds disconnect jumper to power LED
2019-03-08 Moves drill hits near standoff, moves LED jumper down, renames IRQ net to INT, and adds info on other address options
2019-03-08 Updates lightning detector part to latest - window pane of paste rather than solid block
2019-04-24 Removes temp library, the part has been included in the SparkFun Eagle Sensors Library
2019-04-25 Updates Readme
2019-05-16 List of changes in description from v10 to v11
    * Changes three way pull up jumper to disinclude I2C data line - also changes values to 10k
    * Removes seperate I2C header and combines I2C and SPI into one header - prevents extraneous trace length on data lines
    * Improves layout for better ground pour
    * Moves address jumpers and SPI select jumpers
2019-05-17 Improves silk
2019-05-17 Adds "NC" silk, and updates info text in schematic for pullup resistors
2019-05-17 Adds flame to underside (hur hur), adds additional path in bottom pour. changes jumper names to address rather than jumper
2019-05-17 Fixes LED label
2019-05-17 Adds gerbers
2019-06-17 Removes old production files, updates board to default to SPI....
    * Changes three way jumper to normally open - only need pull ups for I2C mode
    * Changes interface select jumper to normally closed (SPI selection)
    * Updates notes on both jumpers for these modes
    * Removes Qwiic Header
2019-06-17 Changes names of board files and does nothing else
2019-06-17 Fixes various trace errors caused by jumper swap in previous commit
2019-06-17 Updates jumper on underside to read I2C rather than SPI
2019-06-17 Fixes minor issues, changes i2c enable jumper label
2019-06-17 Changes chip select pull down to pullup.
2019-06-18 Adds three way jumper for switching to I2C, one that also includes a way to ground Chip select
2019-06-20 Changes VCC range font to vector
2019-06-20 Adds measurements for the standoff holes, rotates CS and SI silk, removes some wire stubs.
2019-06-20 Fixes measurement on wrong layer
2019-06-20 Adds production files
2019-07-23 Fixes interrupt label
2019-07-23 Fixes interrupt label and repanelizes product
2019-07-29 Updates hookup guide link

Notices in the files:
parts and their libraries:
SparkFun-Aesthetics: Licensing: Creative Commons ShareAlike 4.0 International - https://creativecommons.org/licenses/by-sa/4.0
SparkFun-Aesthetics: Released under the Creative Commons Attribution Share-Alike 4.0 License
SparkFun-Aesthetics: https://creativecommons.org/licenses/by-sa/4.0
